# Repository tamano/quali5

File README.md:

# Quali5
Quali5は、シンプルな左手用マクロパッドです。
親指キーでレイヤー切り替え可能な4個のキーで、合計8個のキーとして使う事が出来ます。
(QMK Firmwareを書き換えることでキーアサインは自由に変更可能です)

Quali5 is a simple left-handed macropad.
It can be used as an 8-key keybaord with 2 layered 4 keys which can toggle with a thumb key.
(You can change key assigns with QMK Firmware)

## Documents
- [注文方法 / How to Order](doc/how_to_order.md)
- [組み立て方法 / Build Guide](doc/build_guide.md)
- [キーマップのカスタマイズ方法 / How to Change Keymaps](doc/customize_keymap.md)

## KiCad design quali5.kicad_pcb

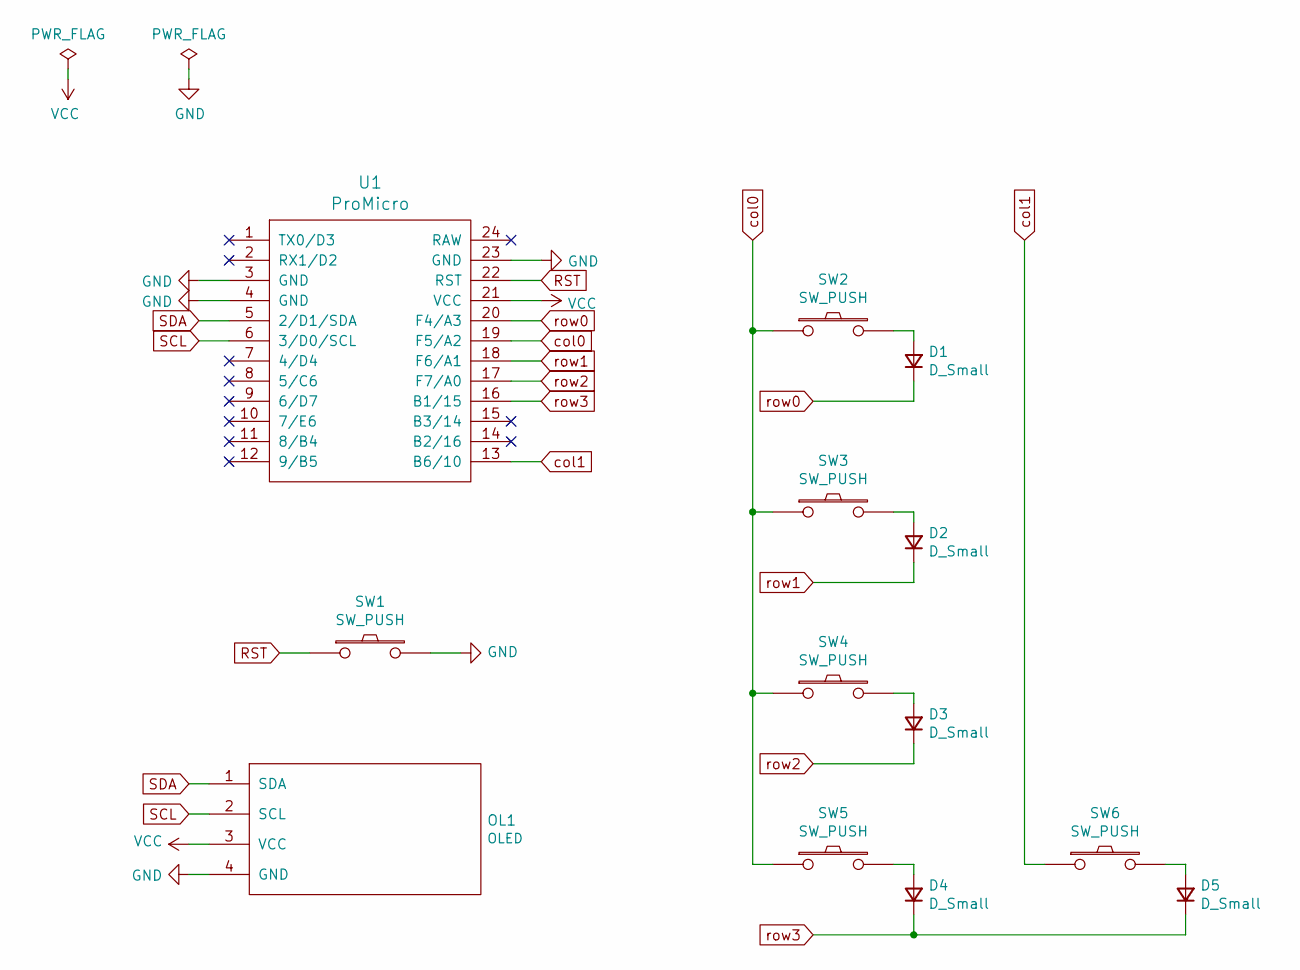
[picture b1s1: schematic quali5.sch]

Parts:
D1, D2, D3, D4, D5: D_Small; D3_SMD
OL1: OLED
SW1: SW_PUSH; ResetSW_1side
SW2, SW3, SW4, SW5, SW6: SW_PUSH; ChocV1_V2_Hotswap
U1: ProMicro; ProMicro_v3.5

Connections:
GND: OL1.4 (GND), SW1.2, U1.3 (GND), U1.4 (GND), U1.23 (GND)
unnamed: D1.2 (A), SW2.2
unnamed: D2.2 (A), SW3.2
unnamed: D3.2 (A), SW4.2
unnamed: D4.2 (A), SW5.2
unnamed: D5.2 (A), SW6.2
RST: SW1.1, U1.22 (RST)
SCL: OL1.2 (SCL), U1.6 (3/D0/SCL)
SDA: OL1.1 (SDA), U1.5 (2/D1/SDA)
VCC: OL1.3 (VCC), U1.21 (VCC)
col0: SW2.1, SW3.1, SW4.1, SW5.1, U1.19 (F5/A2)
col1: SW6.1, U1.13 (B6/10)
row0: D1.1 (K), U1.20 (F4/A3)
row1: D2.1 (K), U1.18 (F6/A1)
row2: D3.1 (K), U1.17 (F7/A0)
row3: D4.1 (K), D5.1 (K), U1.16 (B1/15)

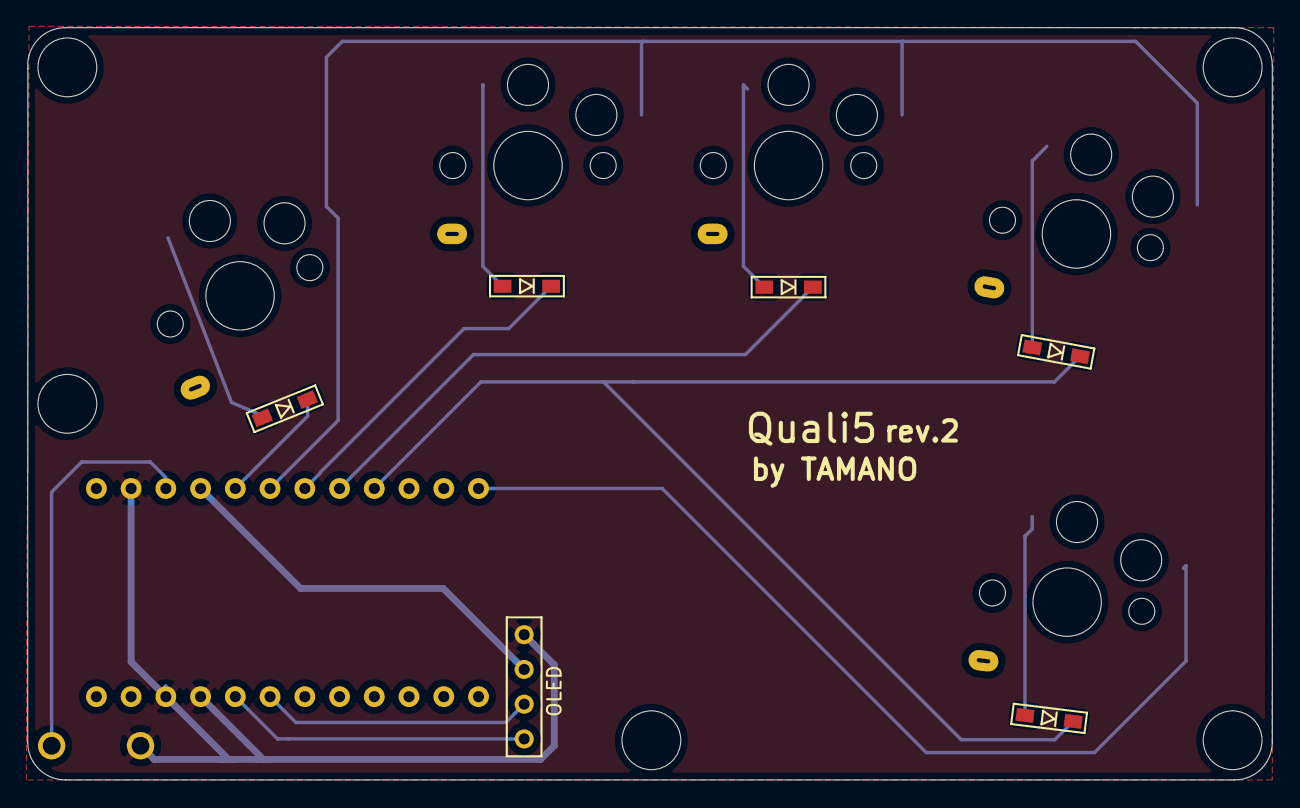
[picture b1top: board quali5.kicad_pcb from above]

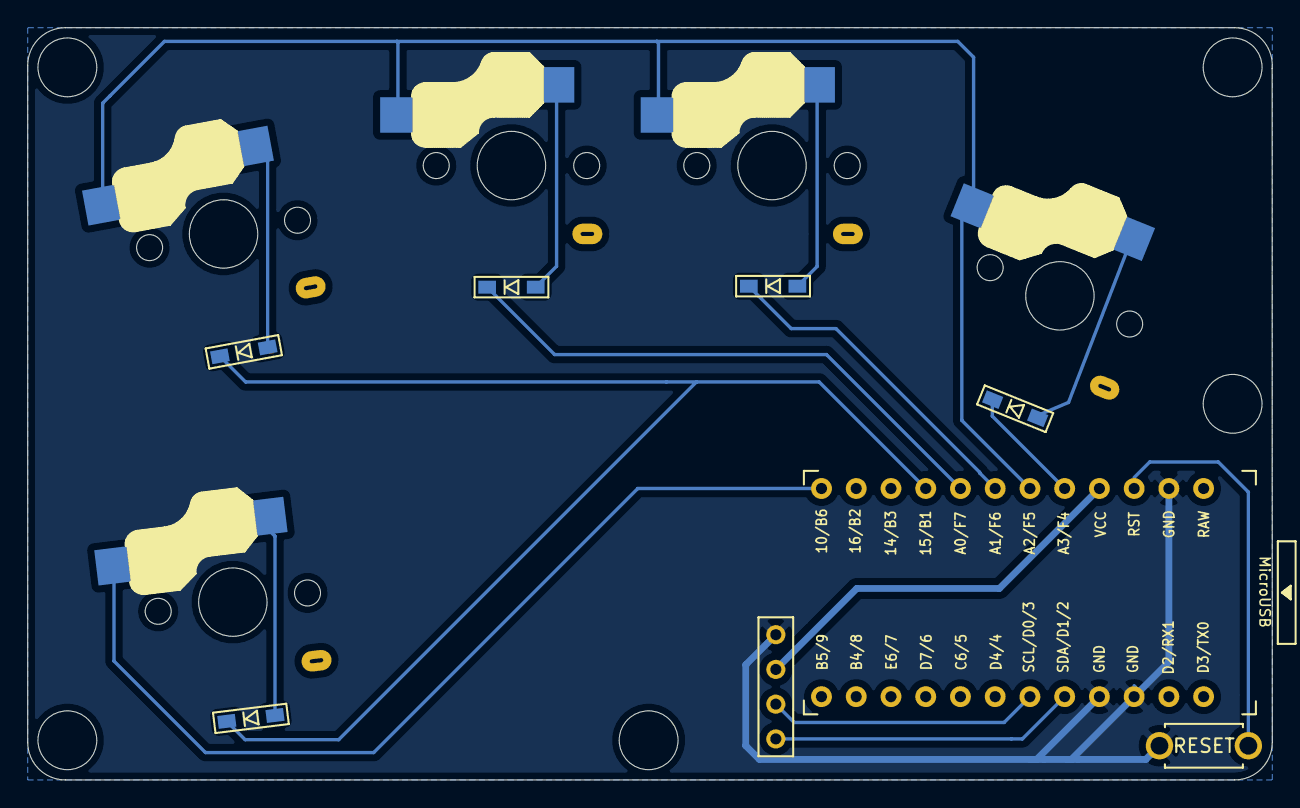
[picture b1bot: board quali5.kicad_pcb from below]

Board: 2 copper layers, 91.0 x 55.0 mm, 18 parts (7 on the bottom side), 16 nets.

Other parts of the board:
Ref**: Val**; M2_HOLE_v2
Ref**#2, Ref**#3, Ref**#4, Ref**#5: Val**; M2_HOLE_v2

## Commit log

2021-05-23 Initialize project with KiCad
2021-05-23 Create circuit diagram.
2021-05-28 Designed PCB footprint
2021-05-28 Create gerber file for PCB.
2021-05-28 Create plate data
2021-05-28 Add .gitignore
2021-05-28 Remove backup file
2021-08-11 Create Plates for rev.2
    mv plate
2021-09-20 First draft of Build Guide
2021-09-20 Change document structure
    To add a chapter about parts/materials
2021-09-20 Add Parts Section
2021-09-20 Add description
2021-09-20 Add build guide (#1)
2021-09-20 Update URL for raw contents
2021-09-20 Add TOC to build guide
2021-10-09 Update build guide
2021-10-09 Updat build guide (Add Remap / VIA support)
2021-10-09 Create How to Order document.
2021-10-09 cosme
2021-10-10 Update Build Guide and Add Customize Keymap
